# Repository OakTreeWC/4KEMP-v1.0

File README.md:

# 4KEMP v1.0

### 4 | the number four
### K | k
### E | ey
### M | macro
### P | pad

4KEMP really just a mini macro pad. Nothing special about it. Can be used to play music games and stuff.
This project was made to help my friend learn how to use KiCad and Fusion360, ~~but then became a [hackclub blueprint](https://blueprint.hackclub.com) project for me as well.~~
To use my project, one can use [vial](https://get.vial.today) to change what each key does, and then use it to run functions on their computer.

## Components

## PCB
pcbs are pretty kewl.
also you just lost the game lol.
### Top

### Bottom

## Soldering
I don't have any documentation from when I was actually doing it, but I do have pics of the final product.
### Top

### Bottom

A lot of my solder joints could be better, it is very inconsistent, and it doesn't look great, but I'm still happy with it.

## Case
I made a few mistakes, and since I neglected to even try to print it at home first, I let them slip, but whatever.

The upper case was 3d printed by JLC 3DP at my own expense in gray resin, which I honestly love the look and feel of. 

However, the lower case is where all the mistakes arose. Stupidity on my part caused these mistakes, but oh well. Because I added neopixels on the bottom and wanted to actually use them, I ordered my lower case in translucent resin. Unfortunately though, I didn't realize that this resin was super vulnerable to warping and had horrible dimensional accuracy. 

When I received the part, I quickly realized how bad it was. Therefore, I attempted to undo the warping with heat and pressure. I ended up pushing it too far though, resulting in a large crack in the base.

Additionally, the poor accuracy caused the top left corner of my macropad to be misaligned. It isn't too bad, but its definitely there.

### Issues

Thin case causing MASSIVE warping.

Attempt to fix warping causing large crack.

Excessive clearance around USB port.

Poor dimensional accuracy of lower case causing horrific misalignment.

## Assembly

Assembly was very straightforward. I first added threaded inserts into my lower case, then put my pcb into the upper case and installed all the switches. After that, I just put the entire upper case/pcb assembly into the lower case, tightened the three M3 bolts, and I was done.

## Bill of Materials
|Item                  |Description                                                                                  |Qty.|Unit Price (USD)|Total Price  (USD)|URL                                                                                                                                                                                                                                                                                                                                                                                                                                                                                                         |Running Total (USD + Tax)|
|----------------------|---------------------------------------------------------------------------------------------|----|----------------|------------------|------------------------------------------------------------------------------------------------------------------------------------------------------------------------------------------------------------------------------------------------------------------------------------------------------------------------------------------------------------------------------------------------------------------------------------------------------------------------------------------------------------|-------------------------|
|XIAO RP2040    |ARM® Cortex®-M0+ MCU 32-Bit Embedded Evaluation Board                                        |1   |$4.68           |$4.68             |https://www.digikey.com/en/products/detail/seeed-technology-co-ltd/102010428/14672129                                                                                                                                                                                                                                                                                                                                                                                                                       |$5.16                    |
|Rotary Encoder        |Rotary Encoder Incremental 24 Quadrature (Incremental) Horizontal                            |1   |$1.72           |$1.72             |https://www.digikey.com/en/products/detail/bourns-inc/PEC12R-4020F-S0024/4699271                                                                                                                                                                                                                                                                                                                                                                                                                            |$7.06                    |
|Reverse Neopixels     |Addressable Lighting - 10 LED Discrete Red, Green, Blue (RGB)                                |1   |$2.95           |$2.95             |https://www.digikey.com/en/products/detail/adafruit-industries-llc/4960/14302512                                                                                                                                                                                                                                                                                                                                                                                                                            |$10.31                   |
|Backlight Neopixels   |Addressable Lighting Neopixel 10 LED Discrete Serial (Shift Register) Red, Green, Blue (RGB) |1   |$4.50           |$4.50             |https://www.digikey.com/en/products/detail/adafruit-industries-llc/1655/5154679                                                                                                                                                                                                                                                                                                                                                                                                                             |$15.27                   |
|Akko Keyboard Switches|Akko V3 Silver Pro Keyboard Switch 5-Pin Linear Pre-Lubed Switches (45pcs)                   |1   |$16.99          |$16.99            |https://www.amazon.com/dp/B0CDW6W2P5?ref=cm_sw_r_cso_cp_apin_dp_HSMA9S87491DNTP9KS93&ref_=cm_sw_r_cso_cp_apin_dp_HSMA9S87491DNTP9KS93&social_share=cm_sw_r_cso_cp_apin_dp_HSMA9S87491DNTP9KS93&th=1                                                                                                                                                                                                                                                                                                         |$34.00                   |
|Schottky Diodes       |Diode 30 V 200mA Surface Mount 0603                                                          |4   |$0.17           |$0.68             |https://www.digikey.com/en/products/detail/taiwan-semiconductor-corporation/TSS54U-RGG/7360711                                                                                                                                                                                                                                                                                                                                                                                                              |$34.75                   |
|Resistor              |For Neopixel Data Line. 379 Ohms ±0.1% 0.1W, 1/10W Chip Resistor 0603 (1608 Metric)          |1   |$0.12           |$0.12             |https://www.digikey.com/en/products/detail/koa-speer-electronics-inc/RN73R1JTTD3790B25/10016392                                                                                                                                                                                                                                                                                                                                                                                                             |$34.88                   |
|PCB                   |PCB Manufactured by JLCPCB. White, 1.6mm, HASL w/ lead                                       |5   |$0.40           |$2.00             |https://jlcpcb.com                                                                                                                                                                                                                                                                                                                                                                                                                                                                                          |$37.09                   |
|Lower Case            |Case Manufactured by JLC3DP. 8001 Resin, Translucent                                         |1   |$2.19           |$2.19             |https://jlc3dp.com                                                                                                                                                                                                                                                                                                                                                                                                                                                                                          |$39.50                   |
|Upper Case            |Case Manufactured by JLCPCB. Black Resin                                                     |1   |$2.43           |$2.43             |https://jlc3dp.com                                                                                                                                                                                                                                                                                                                                                                                                                                                                                          |$42.18                   |
|Keycaps               |DSA Keycaps White 24pcs                                                                      |1   |$8.99           |$8.99             |www.amazon.com/Mechkeeb-Profile-Switches-Keyboard-Replacement/dp/B0BWDTBF1L                                                                                                                                                                                                                                                                                                                                                                                                                                 |$52.09                   |
|Rotary Encoder Knob   |Aluminum Rotary Encoder Knob 2pcs                                                            |1   |$8.99           |$8.99             |www.amazon.com/Szliyands-Aluminum-Electronic-Potentiometer-Knob，Switch/dp/B099PX52LW                                                                                                                                                                                                                                                                                                                                                                                                                        |$62.00                   |
|Threaded Inserts      |M3 Threaded Inserts 152pcs                                                                   |1   |$6.99           |$6.99             |https://www.amazon.com/Vibit-Threaded-Soldering-Printing-Components/dp/B0FWWW8VP1/ref=sr_1_3                                                                                                                                                                                                                                                                                                                                                                                                                |$69.71                   |
|Machine Screws        |M3 Screw Kit                                                                                 |1   |$9.99           |$9.99             |https://www.amazon.com/Fgruh-750PCS-Assortment-Washers-Assorted/dp/B0FGV5FCBN/ref=sr_1_3?crid=2UNAGQJ7TRSPF&dib=eyJ2IjoiMSJ9.T3HWVrCMzkskj4FDtvfCYjAhiKf2eIXJNrTn39_bFjBR1J806O1NskeC_TrNL2d-0_rv4c3tJ2WiIqImzYRsNdlKskiq_KPhw2MnuLHrr7ROWvp0aYAezCjHHAfx-j9R1FgRYMZR6z3j6DWbe_FTcKSI5cNCdqJEDhLnH9UyM0u5ed6Of07kpRqKBp5WkTLn8qUsW4GWJz8Y-hXZX6mGeCbl1zGSf24ox8LtrZCSgZs.QTs0QwFb8cDs_wXvUWLPa0GUjuv97zXGykg1SJQzuNE&dib_tag=se&keywords=m3+screw+set&qid=1771132139&sprefix=m3+screw+set%2Caps%2C211&sr=8-3|$80.72                   |
|Digikey Shipping      |                                                                                             |1   |$4.99           |$4.99             |                                                                                                                                                                                                                                                                                                                                                                                                                                                                                                            |$86.22                   |
|JLC Shipping          |                                                                                             |1   |$8.93           |$8.93             |                                                                                                                                                                                                                                                                                                                                                                                                                                                                                                            |$96.07                   |

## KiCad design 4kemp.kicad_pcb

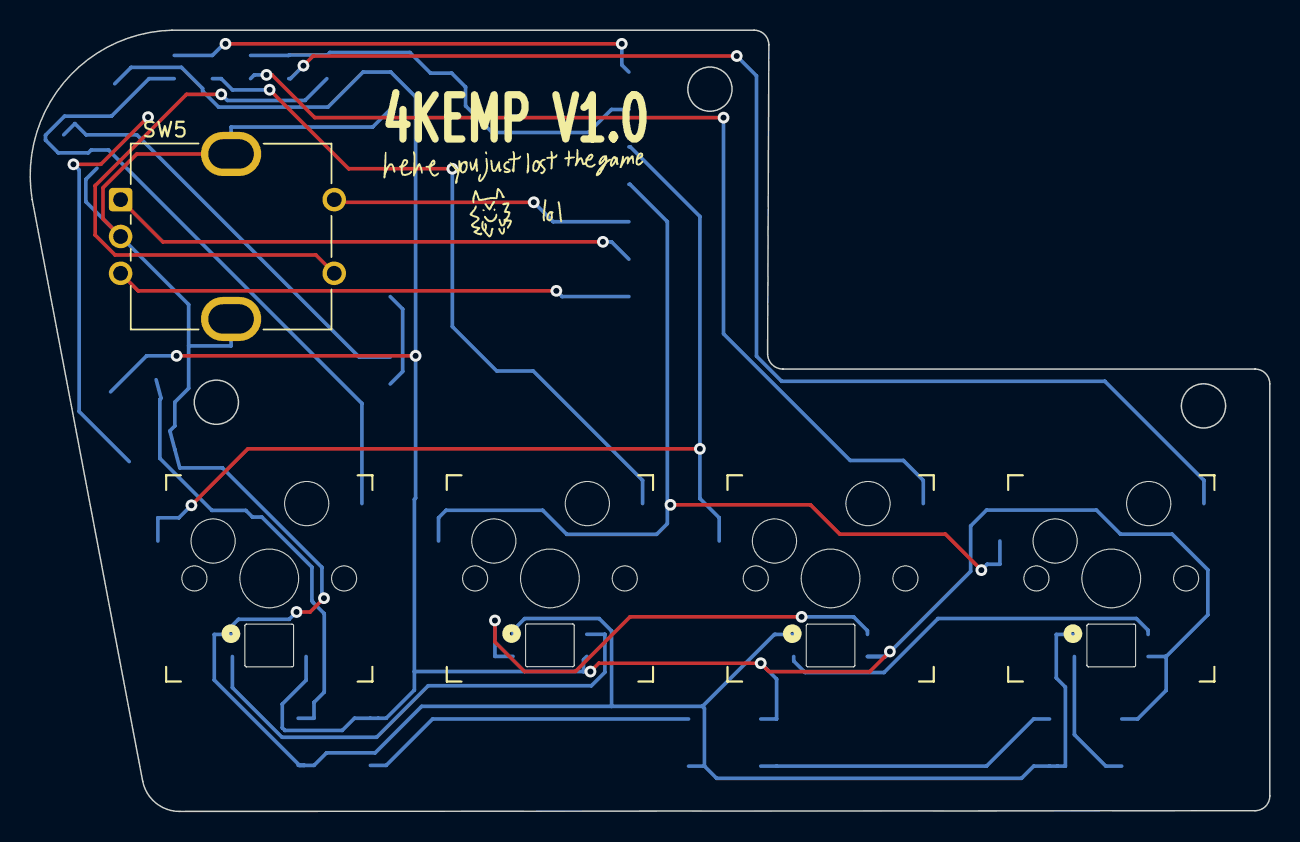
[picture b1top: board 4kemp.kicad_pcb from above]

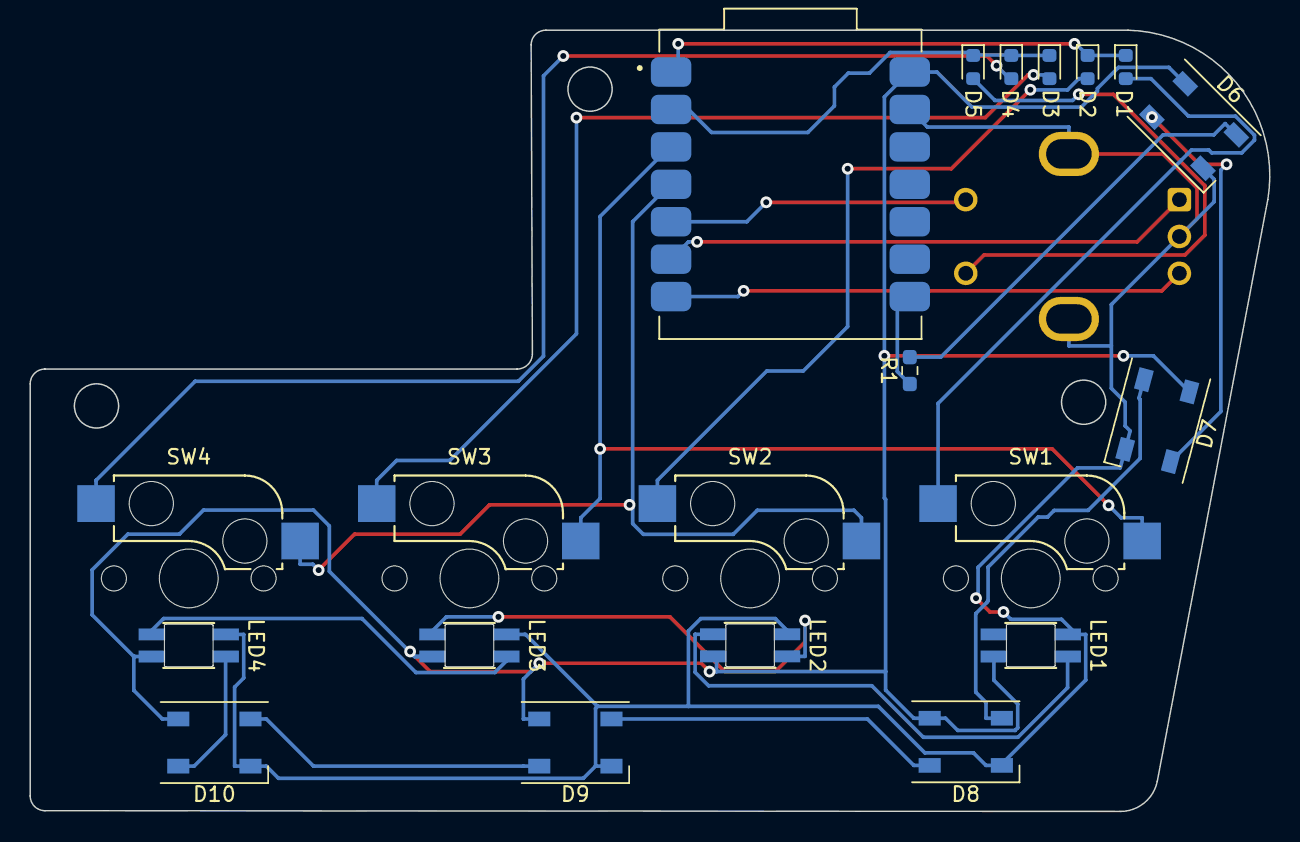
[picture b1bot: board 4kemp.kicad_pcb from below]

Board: 2 copper layers, 84.1 x 53.0 mm, 21 parts (16 on the bottom side), 24 nets.

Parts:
D1, D2, D3, D4, D5: D_Schottky; D_0603_1608Metric
D6, D7, D8, D9, D10: NeoPixel_THT; LED_SK6812_PLCC4_5.0x5.0mm_P3.2mm
LED1, LED2, LED3, LED4: 4960; 4960_ADA
R1: 330o; R_0603_1608Metric_Pad0.98x0.95mm_HandSolder
SW1, SW2, SW3, SW4: SW_Push_SPDT; Kailh_socket_MX
SW5: RotaryEncoder_Switch; RotaryEncoder_Bourns_Vertical_PEC12R-3x17F-Sxxxx
U1: 102010428; MODULE_102010428

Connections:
+5V: D6.3 (VDD), D7.3 (VDD), D8.3 (VDD), D9.3 (VDD), D10.3 (VDD), LED1.1 (VDD), LED2.1 (VDD), LED3.1 (VDD), LED4.1 (VDD), U1.14 (5V)
/A: SW5.A, U1.6 (P7/SCL/D5)
/B: SW5.B, U1.7 (P0//TX/D6)
/Column0: SW1.2 (B), SW3.2 (B), U1.3 (P28/A2/D2)
/Column1: SW2.2 (B), SW4.2 (B), U1.4 (P29/A3/D3)
/Column2: SW5.S1, U1.5 (P6/SDA/D4)
/NP2DATA: D10.4 (DOUT), LED4.4 (DIN)
/NPDATA: D6.2 (DIN), R1.2
/Row0: D1.1 (K), D2.1 (K), U1.1 (P26/A0/D0)
/Row1: D3.1 (K), D4.1 (K), D5.1 (K), U1.2 (P27/A1/D1)
GND: D6.1 (VSS), D7.1 (VSS), D8.1 (VSS), D9.1 (VSS), D10.1 (VSS), LED1.3 (GND), LED2.3 (GND), LED3.3 (GND), LED4.3 (GND), SW5.C, SW5.SH (SHIELD), U1.13 (GND)
unnamed: D1.2 (A), SW1.1 (A)
unnamed: D2.2 (A), SW2.1 (A)
unnamed: D3.2 (A), SW3.1 (A)
unnamed: D4.2 (A), SW4.1 (A)
unnamed: D5.2 (A), SW5.S2
unnamed: D6.4 (DOUT), D7.2 (DIN)
unnamed: D7.4 (DOUT), D8.2 (DIN)
unnamed: D8.4 (DOUT), D9.2 (DIN)
unnamed: D9.4 (DOUT), D10.2 (DIN)
unnamed: LED1.4 (DIN), LED2.2 (DOUT)
unnamed: LED2.4 (DIN), LED3.2 (DOUT)
unnamed: LED3.4 (DIN), LED4.2 (DOUT)
unnamed: R1.1, U1.8 (D7/CSB/P1/RX)

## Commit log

2026-02-08 Made everything
2026-02-08 Create README.md for 4KEMP project
    Added a README file for the 4KEMP project with descriptions and images.
2026-02-15 Add Bill of Materials to README
    Added a Bill of Materials section with item details and pricing.
2026-02-15 Fix link formatting in README.md
2026-02-15 Fix typo in BOM
    Updated item name in the Bill of Materials section.
2026-02-15 Added 4KEMP.step
2026-02-27 Moved KiCad Files to dedicated folder
2026-02-27 Update project description in README.md
    Removed the mention of the project becoming a hackclub blueprint.
    Apparently one cannot make more than one macropad.
2026-05-07 added firmware source
2026-05-31 Update README with image and formatting changes
    Added an image and updated the README format.
2026-05-31 Expand README with detailed project sections
    Added sections for components, PCB, soldering, case issues, and assembly details.
